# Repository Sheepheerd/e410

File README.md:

# E410

This is an RC Car running off of an ESP-32S and communicating with another ESP-32S Gesture Glove.

# Bill of Materials

| Purpose        | Item                                                                                                                                                                                                                                                                                                                                                          | Price  |
| :------------- | :------------------------------------------------------------------------------------------------------------------------------------------------------------------------------------------------------------------------------------------------------------------------------------------------------------------------------------------------------------ | :----- | --- |
| Brains         | 2 x [ESP-32S](https://www.amazon.com/dp/B0CR5Y2JVD?ref=ppx_yo2ov_dt_b_fed_asin_title&th=1)                                                                                                                                                                                                                                                                    | \$18   |
| Motor Driver   | [TB6612FNG](https://www.sparkfun.com/sparkfun-motor-driver-dual-tb6612fng-1a.html)                                                                                                                                                                                                                                                                            | \$15   |
| IMU            | [MPU-6050](https://www.amazon.com/HiLetgo-MPU-6050-Accelerometer-Gyroscope-Converter/dp/B01DK83ZYQ/145-9389697-4887616?pd_rd_w=uXXXS&content-id=amzn1.sym.aa738fbd-ad05-4d11-aae2-04b598db6305&pf_rd_p=aa738fbd-ad05-4d11-aae2-04b598db6305&pf_rd_r=SY5VKKQA8W10JFKG62G2&pd_rd_wg=V9QPU&pd_rd_r=8fcda28f-cfcc-457b-9a6a-7c448a094ec9&pd_rd_i=B00LP25V1A&th=1) | \$7.00 |
| Throttle       | [Flex Sensor 2.2"](https://www.amazon.com/dp/B07MHTWR1C?ref=ppx_yo2ov_dt_b_fed_asin_title)                                                                                                                                                                                                                                                                    | \$9    |
| Buck Converter | [MP1584EN](https://www.amazon.com/dp/B0B779ZYN1?ref=ppx_yo2ov_dt_b_fed_asin_title&th=1)                                                                                                                                                                                                                                                                       | 10     |
|                |                                                                                                                                                                                                                                                                                                                                                               |        | 49  |

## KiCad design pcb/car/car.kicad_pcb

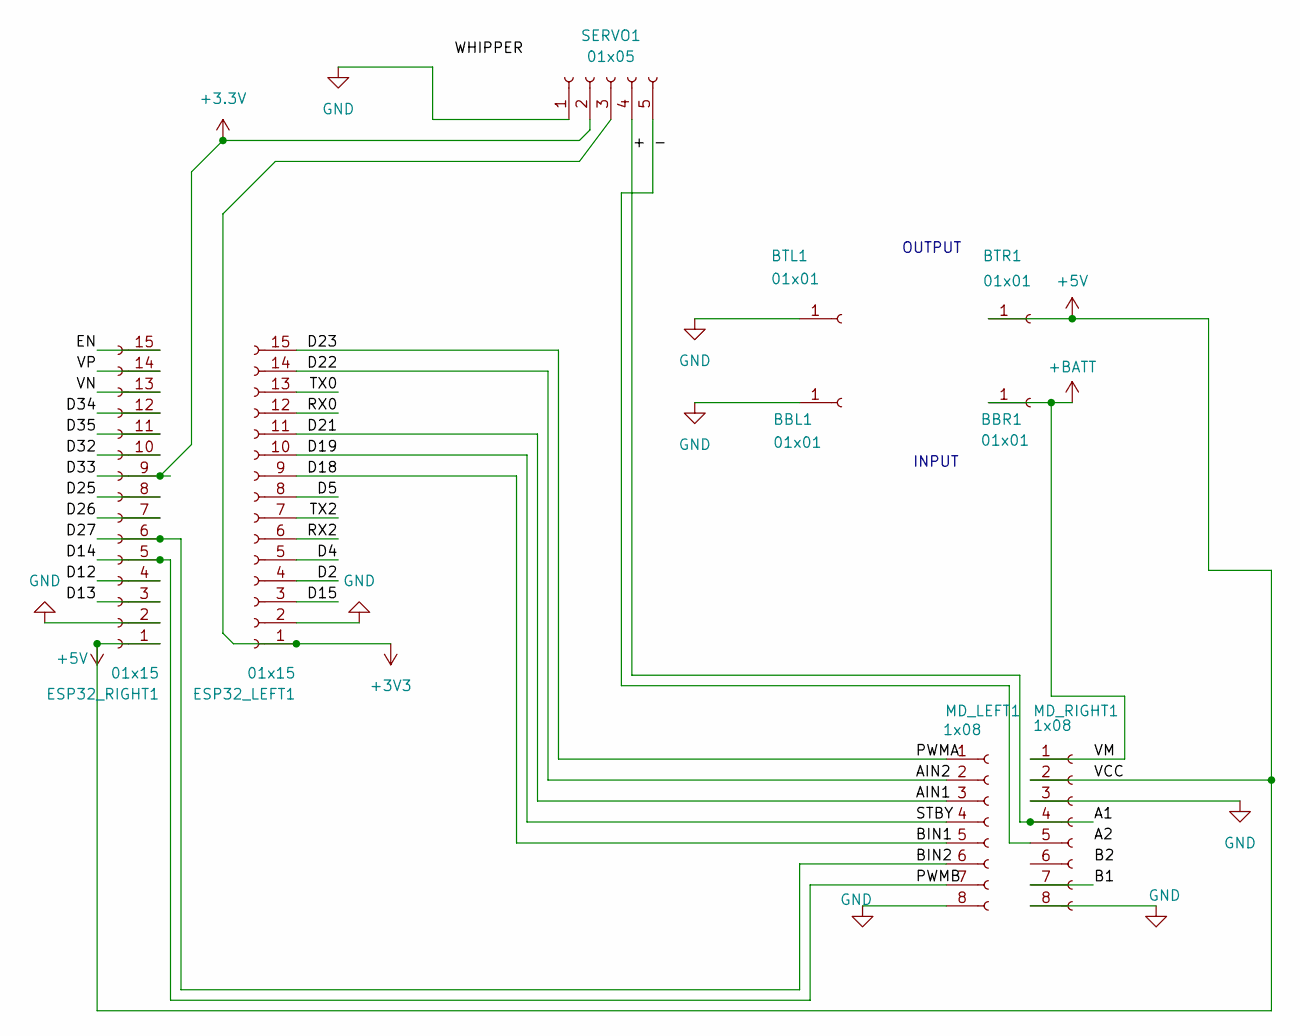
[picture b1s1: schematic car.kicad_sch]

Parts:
BBL1: 01x01; PinSocket_1x01_P2.54mm_Vertical
BBR1: 01x01; PinSocket_1x01_P2.54mm_Vertical
BTL1: 01x01; PinSocket_1x01_P2.54mm_Vertical
BTR1: 01x01; PinSocket_1x01_P2.54mm_Vertical
ESP32_LEFT1, ESP32_RIGHT1: 01x15; PinSocket_1x15_P2.54mm_Vertical
MD_LEFT1: 1x08; PinSocket_1x08_P2.54mm_Vertical
MD_RIGHT1: 1x08; PinSocket_1x08_P2.54mm_Vertical
SERVO1: 01x05; PinSocket_1x05_P2.00mm_Vertical

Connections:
+3.3V: ESP32_RIGHT1.9, SERVO1.2
+3V3: ESP32_LEFT1.1, SERVO1.3
+5V: BTR1.1, ESP32_RIGHT1.1, MD_RIGHT1.2
+BATT: BBR1.1, MD_RIGHT1.1
/+: MD_RIGHT1.4, SERVO1.4
/-: MD_RIGHT1.5, SERVO1.5
/AIN1: ESP32_LEFT1.11, MD_LEFT1.3
/AIN2: ESP32_LEFT1.14, MD_LEFT1.2
/B1: MD_RIGHT1.7
/BIN1: ESP32_LEFT1.9, MD_LEFT1.5
/BIN2: ESP32_RIGHT1.6, MD_LEFT1.6
/D2: ESP32_LEFT1.4
/D4: ESP32_LEFT1.5
/D5: ESP32_LEFT1.8
/D12: ESP32_RIGHT1.4
/D13: ESP32_RIGHT1.3
/D14: ESP32_RIGHT1.5, MD_LEFT1.7
/D15: ESP32_LEFT1.3
/D19: ESP32_LEFT1.10, MD_LEFT1.4
/D23: ESP32_LEFT1.15, MD_LEFT1.1
/D25: ESP32_RIGHT1.8
/D26: ESP32_RIGHT1.7
/D32: ESP32_RIGHT1.10
/D34: ESP32_RIGHT1.12
/D35: ESP32_RIGHT1.11
/EN: ESP32_RIGHT1.15
/RX0: ESP32_LEFT1.12
/RX2: ESP32_LEFT1.6
/TX0: ESP32_LEFT1.13
/TX2: ESP32_LEFT1.7
/VN: ESP32_RIGHT1.13
/VP: ESP32_RIGHT1.14
GND: BBL1.1, BTL1.1, ESP32_LEFT1.2, ESP32_RIGHT1.2, MD_LEFT1.8, MD_RIGHT1.3, MD_RIGHT1.8, SERVO1.1

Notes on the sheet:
OUTPUT
INPUT

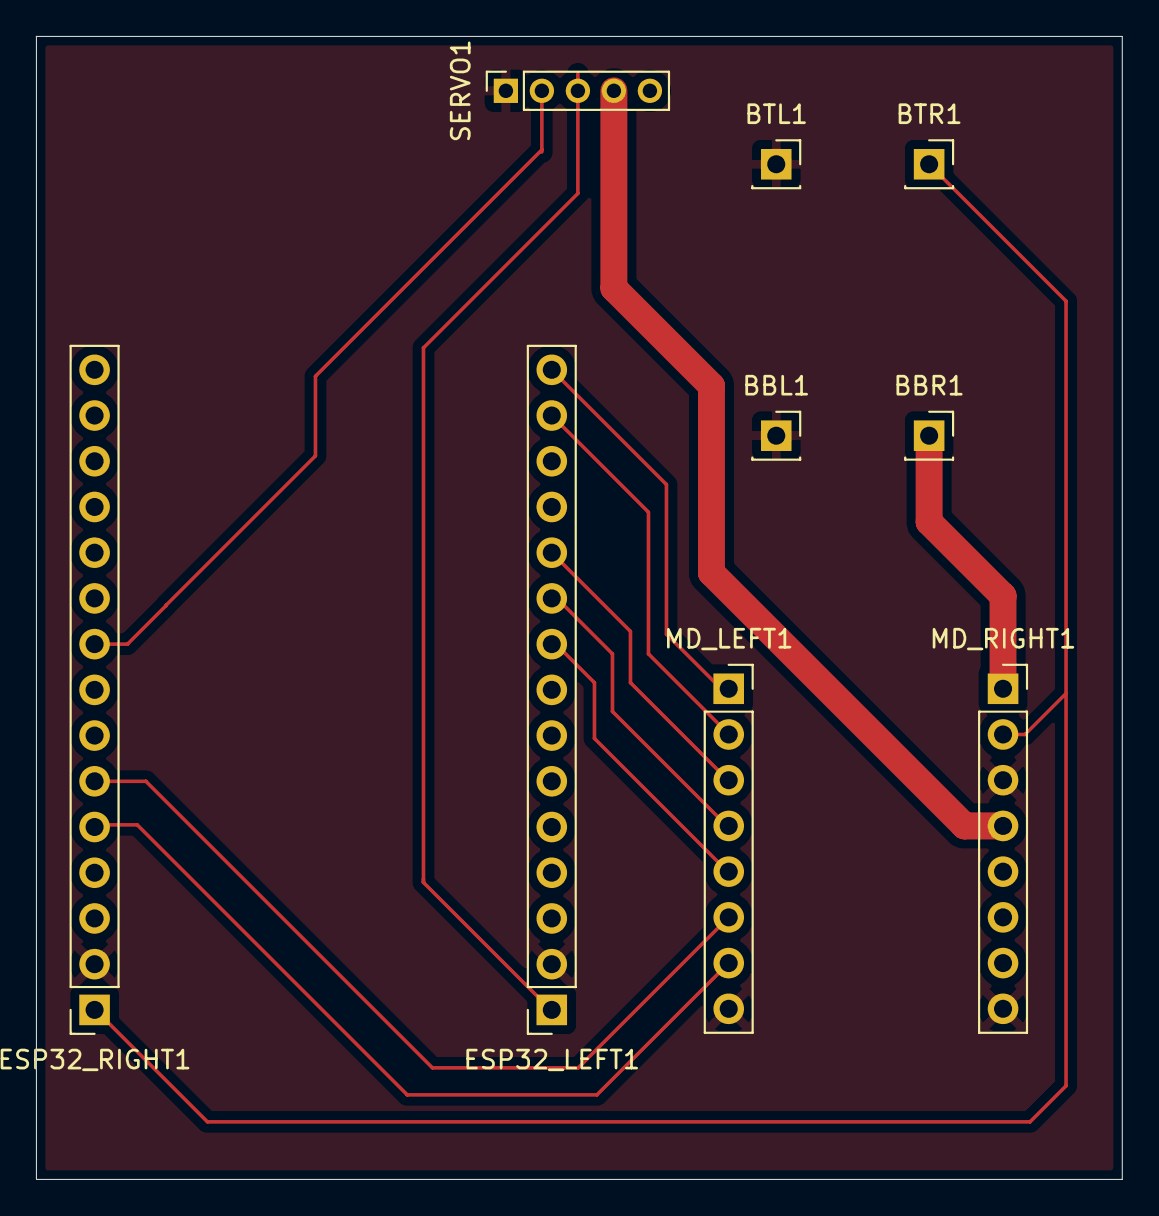
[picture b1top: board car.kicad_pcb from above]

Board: 2 copper layers, 60.3 x 63.5 mm, 9 parts (0 on the bottom side), 14 nets.

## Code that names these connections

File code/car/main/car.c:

#include "driver/gpio.h"
#include "driver/ledc.h"
#include "esp_adc/adc_oneshot.h"
#include "freertos/FreeRTOS.h"
#include "freertos/task.h"
#include <stdio.h>

// Define our pins
#define PIN_PWMA 23
#define PIN_AIN2 22
#define PIN_AIN1 21
#define PIN_STBY 19
#define PIN_WHIPPER 33
#define ADC_CHAN ADC_CHANNEL_5 // GPIO 33

#define PIN_PWMB 14
#define PIN_BIN2 27
#define PIN_BIN1 18

#define SAFE_MAX_DUTY 600 // Cap at ~60% power to stay near 1A
#define RAMP_STEP 25      // How much to increase duty each step
#define RAMP_DELAY_MS 10  // Speed of the ramp

static int current_rear_duty = 0;
adc_oneshot_unit_handle_t adc1_handle;

adc_oneshot_unit_handle_t adc1_handle;

void init_hardware() {
  // 1. Setup Control Pins
  gpio_config_t io_conf = {
      .pin_bit_mask = (1ULL << PIN_AIN1) | (1ULL << PIN_AIN2) |
                      (1ULL << PIN_STBY) | (1ULL << PIN_BIN1) |
                      (1ULL << PIN_BIN2),
      .mode = GPIO_MODE_OUTPUT,
  };
  gpio_config(&io_conf);
  gpio_set_level(PIN_STBY, 1); // Enable Driver

  // 2. Setup PWM (Speed)
  ledc_timer_config_t ledc_timer = {
      .speed_mode = LEDC_LOW_SPEED_MODE,
      .duty_resolution = LEDC_TIMER_10_BIT,
      .timer_num = LEDC_TIMER_0,
      .freq_hz = 10000, // 10kHz for smooth motor movement
      .clk_cfg = LEDC_AUTO_CLK};
  ledc_timer_config(&ledc_timer);

  ledc_channel_config_t channel_a = {.speed_mode = LEDC_LOW_SPEED_MODE,
                                     .channel = LEDC_CHANNEL_0,
                                     .timer_sel = LEDC_TIMER_0,
                                     .intr_type = LEDC_INTR_DISABLE,
                                     .gpio_num = PIN_PWMA,
                                     .duty = 0,
                                     .hpoint = 0};
  ledc_channel_config(&channel_a);

  ledc_channel_config_t channel_b = {.speed_mode = LEDC_LOW_SPEED_MODE,
                                     .channel = LEDC_CHANNEL_1,
                                     .timer_sel = LEDC_TIMER_0,
                                     .intr_type = LEDC_INTR_DISABLE,
                                     .gpio_num = PIN_PWMB,
                                     .duty = 0,
                                     .hpoint = 0};
  ledc_channel_config(&channel_b);

  // 3. Setup ADC (Position Feedback)
  adc_oneshot_unit_init_cfg_t init_config1 = {.unit_id = ADC_UNIT_1};
  adc_oneshot_new_unit(&init_config1, &adc1_handle);
  adc_oneshot_chan_cfg_t config = {
      .bitwidth = ADC_BITWIDTH_DEFAULT,
      .atten = ADC_ATTEN_DB_12, // Allows reading full 0-3.3V range
  };
  adc_oneshot_config_channel(adc1_handle, ADC_CHAN, &config);
}

void drive_whipper(int target_val) {
  int current_val;
  int tolerance = 40; // Stop within this range to prevent "jitter"

  while (1) {
    adc_oneshot_read(adc1_handle, ADC_CHAN, &current_val);
    int error = target_val - current_val;

    if (abs(error) < tolerance) {
      // Target Reached: Stop Motor
      ledc_set_duty(LEDC_LOW_SPEED_MODE, LEDC_CHANNEL_0, 0);
      ledc_update_duty(LEDC_LOW_SPEED_MODE, LEDC_CHANNEL_0);
      break;
    }

    // Set Direction
    if (error > 0) {
      gpio_set_level(PIN_AIN1, 0);
      gpio_set_level(PIN_AIN2, 1);
    } else {
      gpio_set_level(PIN_AIN1, 1);
      gpio_set_level(PIN_AIN2, 0);
    }

    // Set Speed (Slow down as we get closer)
    int speed = abs(error) > 200 ? 700 : 400; // 0 to 1023 range
    ledc_set_duty(LEDC_LOW_SPEED_MODE, LEDC_CHANNEL_0, speed);
    ledc_update_duty(LEDC_LOW_SPEED_MODE, LEDC_CHANNEL_0);

    vTaskDelay(pdMS_TO_TICKS(10));
  }
}

void drive_rear(int target_speed) {
  // 1. Constrain to safety limits
  if (target_speed > SAFE_MAX_DUTY)
    target_speed = SAFE_MAX_DUTY;
  if (target_speed < -SAFE_MAX_DUTY)
    target_speed = -SAFE_MAX_DUTY;

  // 2. Set Direction Logic
  if (target_speed >= 0) {
    gpio_set_level(PIN_BIN1, 1);
    gpio_set_level(PIN_BIN2, 0);
  } else {
    gpio_set_level(PIN_BIN1, 0);
    gpio_set_level(PIN_BIN2, 1);
  }

  int target_duty = abs(target_speed);

  // 3. Ramping Logic: Gradually move current_duty toward target_duty
  while (current_rear_duty != target_duty) {
    if (current_rear_duty < target_duty) {
      current_rear_duty += RAMP_STEP;
      if (current_rear_duty > target_duty)
        current_rear_duty = target_duty;
    } else {
      current_rear_duty -= RAMP_STEP;
      if (current_rear_duty < target_duty)
        current_rear_duty = target_duty;
    }

    ledc_set_duty(LEDC_LOW_SPEED_MODE, LEDC_CHANNEL_1, current_rear_duty);
    ledc_update_duty(LEDC_LOW_SPEED_MODE, LEDC_CHANNEL_1);
    vTaskDelay(pdMS_TO_TICKS(RAMP_DELAY_MS));
  }
}

void app_main(void) {
  init_hardware();

  while (1) {
    drive_rear(128);
    drive_whipper(3500);

    vTaskDelay(pdMS_TO_TICKS(2000));

    // Stop driving and steer left
    drive_rear(0);
    drive_whipper(150);

    vTaskDelay(pdMS_TO_TICKS(2000));
  }
}

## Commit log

2026-02-24 feat: BOM
2026-02-24 fix: wrong format
2026-02-25 feat: updating bom
2026-02-25 feat: correct project configuring
2026-03-09 feat: do not know how to do pcb
2026-03-09 feat: clean up and adding mpu6050
2026-03-09 feat: cleaning up pdb
2026-03-11 feat: cleaning up pcb
2026-03-16 feat: increasing trace width
2026-03-16 feat: kicad update
2026-04-13 feat: update pcb, update car code
2026-04-16 feat: flex res working, must work on esp-now
